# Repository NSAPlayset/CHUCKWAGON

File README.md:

#CHUCKWAGON Firmware

This is the demo code used during our [DEF CON 22 talk](https://www.defcon.org/html/defcon-22/dc-22-speakers.html#Datko). The full slides are [here](https://cryptotronix.files.wordpress.com/2014/08/dc_22_diy_hardware_implant.pdf).

The Arduino sketch can be uploaded to the ATmega32p on the [CryptoCape](https://www.sparkfun.com/products/12773) and the bash scripts are used by the target and host.

## Hardware Files

In the Hardware folder, you'll find the schematic, EAGLE CAD files, and BOM for the CHUCKWAGON. You can get the board directly from [OSH Park](https://oshpark.com/shared_projects/FfikIrhc).

### Connecting the CHUCKWAGON

Attach the male VGA adapter to your target. The LED will indicate if power is being supplied from your target. If so, then you can probably receive up to 1A for your implant. If you are using a 5V Logic system, use the SDA and SCL pins directly. If you are using a 3.3V system, use the 3.3V versions. If you do this, you must supply 3.3V to the 3.3V pin.

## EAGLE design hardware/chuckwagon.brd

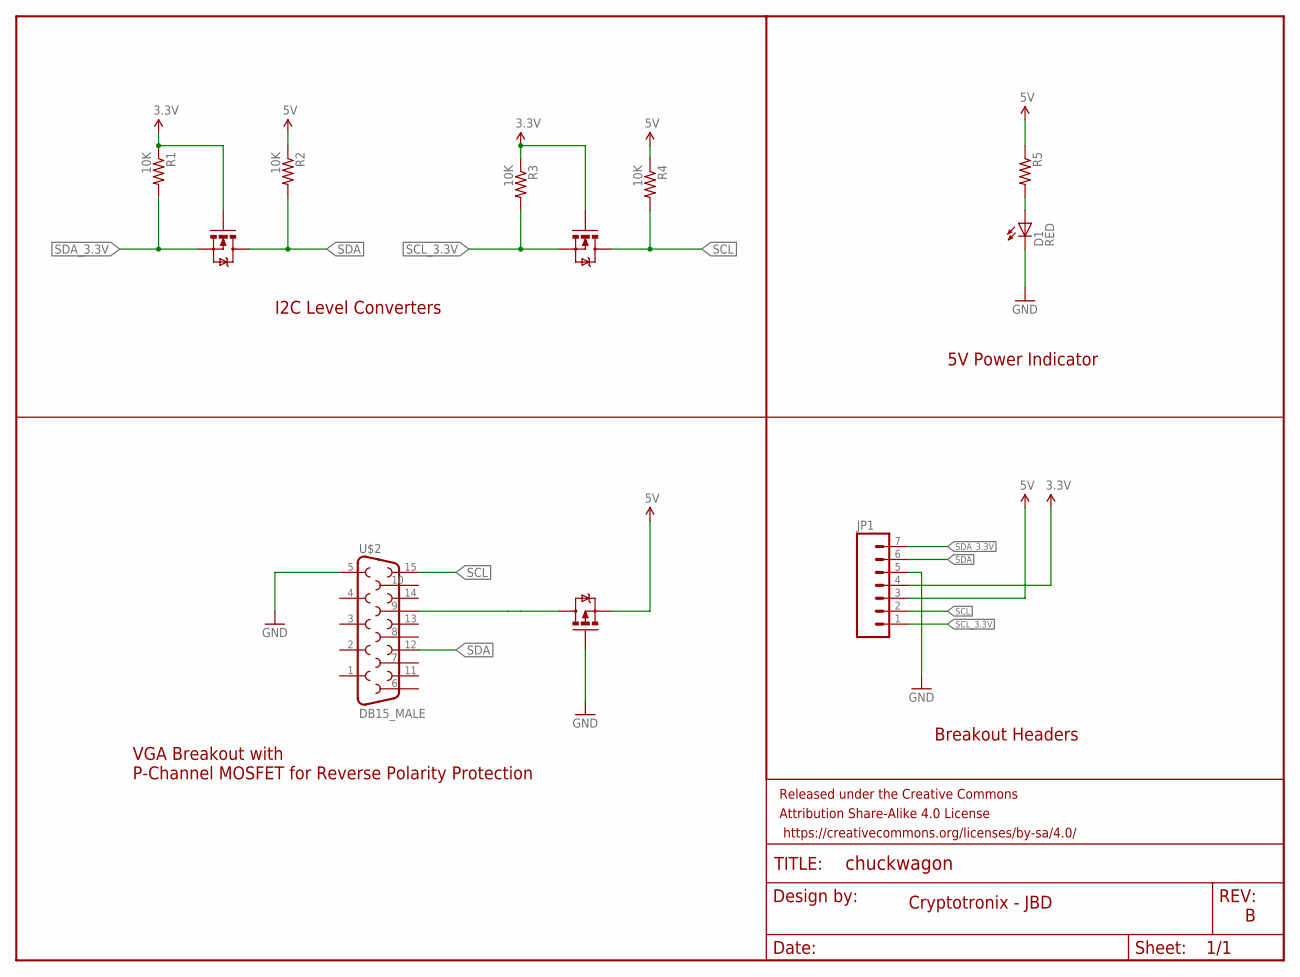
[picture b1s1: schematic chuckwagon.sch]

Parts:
D1: RED; LED-0603
FRAME1: FRAME-LETTER; CREATIVE_COMMONS
JP1: M07; 1X07
Q1, Q2: MOSFET-NCHANNELBSS123LT1G; SOT23
Q3: MOSFET-PCHANNEL; SOT23-3
R1, R2, R3, R4: 10K; 0603-RES
R5: RESISTOR0603-RES; 0603-RES
U$2: DB15_MALE

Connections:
3.3V: JP1.4, Q1.1 (G), Q2.1 (G), R1.1, R3.1
5V: JP1.3, Q3.2 (S), R2.1, R4.1, R5.1
GND: D1.C, JP1.5, Q3.1 (G), U$2.5
unnamed: D1.A, R5.2
unnamed: Q3.3 (D), U$2.9
SCL: JP1.2, Q2.3 (D), R4.2, U$2.15
SCL_3.3V: JP1.1, Q2.2 (S), R3.2
SDA: JP1.6, Q1.3 (D), R2.2, U$2.12
SDA_3.3V: JP1.7, Q1.2 (S), R1.2

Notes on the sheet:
I2C Level Converters
Breakout Headers
VGA Breakout with P-Channel MOSFET for Reverse Polarity Protection
5V Power Indicator
Cryptotronix - JBD

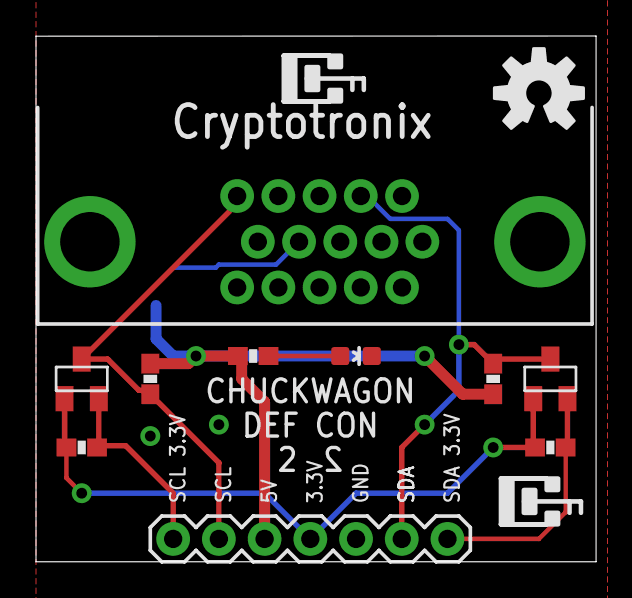
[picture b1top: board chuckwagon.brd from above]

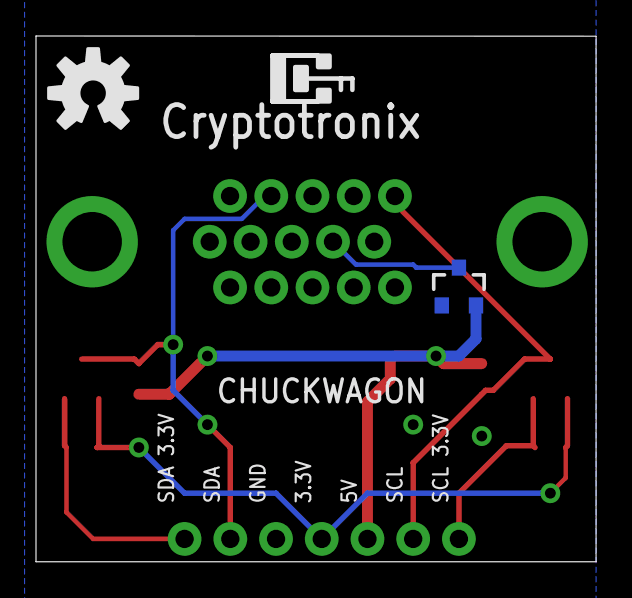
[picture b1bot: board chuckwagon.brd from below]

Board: 2 copper layers, 31.1 x 29.2 mm, 14 parts (2 on the bottom side), 9 nets.

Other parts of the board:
U$1, U$3: OSHW-LOGO-M

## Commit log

2014-07-24 Adds landing page.
2014-08-06 Adds initial chuckwagon cli.
2014-08-06 Adds banner to readme.
2014-08-06 Adds initial arduino sketch.
2014-08-06 Adds make install target.
2014-08-07 Adds scripts
2014-08-07 Moves the sed portion to chuck2exec
2014-08-09 Removes trailing newline
2014-08-10 Updates readme.
2014-08-13 Adds hardware files
2014-08-13 adds schematic
2014-08-13 Updates README
2014-08-13 Adds link to CryptoCape.

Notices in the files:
parts and their libraries:
SparkFun-Aesthetics: Licensing: Creative Commons ShareAlike 4.0 International - https://creativecommons.org/licenses/by-sa/4.0
SparkFun-Aesthetics: Released under the Creative Commons Attribution Share-Alike 4.0 License
SparkFun-Aesthetics: https://creativecommons.org/licenses/by-sa/4.0
